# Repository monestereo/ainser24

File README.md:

##Eagle-Files for a 24 input multiplexer using the Microchip MCP3208 i2c ADC

For more information and licensing visit: [ucapps/midibox](http://www.ucapps.de/mbhp_ainser64.html)

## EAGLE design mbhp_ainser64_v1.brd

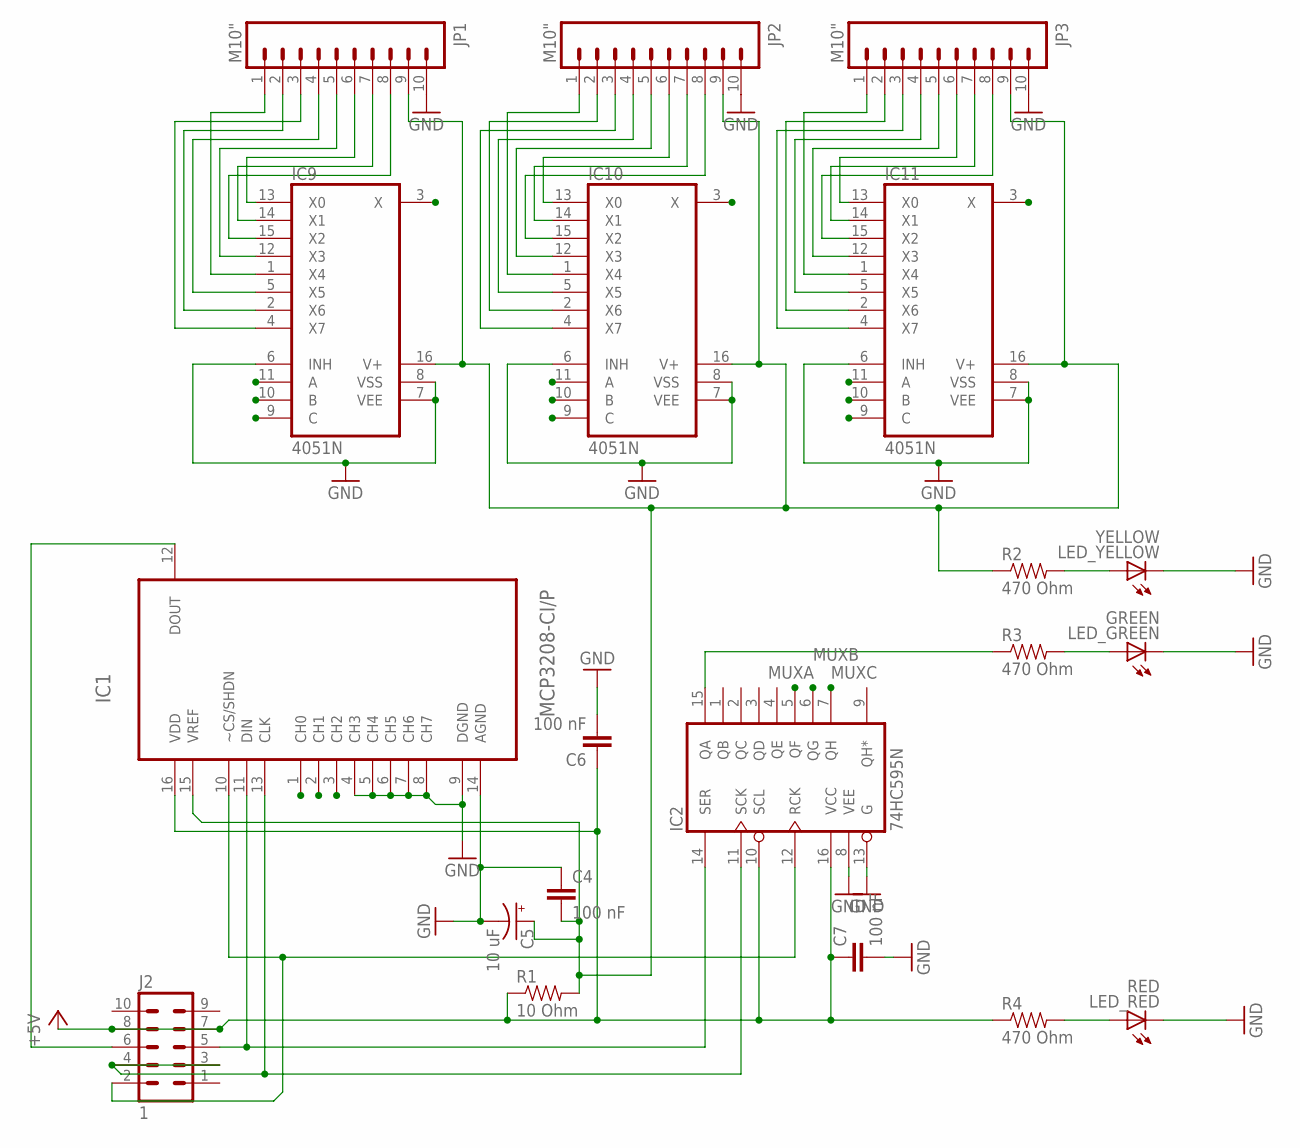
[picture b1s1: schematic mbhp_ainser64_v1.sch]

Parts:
C4, C6, C7: 100 nF; CAP-PTH-5MM
C5: 10 uF; CPOL-RADIAL-10UF-25V
IC1: MCP3208-CI/P; DIP254P762X432-16
IC2: 74HC595N; DIL16
IC9, IC10, IC11: 4051N; DIL16
J2: 1; MA05-2
JP1, JP2, JP3: M10"; 1X10
LED_GREEN: GREEN; LED3MM-NS
LED_RED: RED; LED3MM-NS
LED_YELLOW: YELLOW; LED3MM-NS
R1: 10 Ohm; AXIAL-0.3
R2, R3, R4: 470 Ohm; AXIAL-0.3

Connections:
+5V: C6.1, C7.1, IC1.16 (VDD), IC2.10 (SCL), IC2.16 (VCC), J2.7, J2.8, R1.P$1 (1), R4.P$1 (1)
CH0: IC1.1 (CH0), IC11.3 (X)
CH1: IC1.2 (CH1), IC10.3 (X)
CH2: IC1.3 (CH2), IC9.3 (X)
GND: C4.1, C5.2 (-), C6.2, C7.2, IC1.4 (CH3), IC1.5 (CH4), IC1.6 (CH5), IC1.7 (CH6), IC1.8 (CH7), IC1.9 (DGND), IC1.14 (AGND), IC2.8 (VEE), IC2.13 (G), IC9.6 (INH), IC9.7 (VEE), IC9.8 (VSS), IC10.6 (INH), IC10.7 (VEE), IC10.8 (VSS), IC11.6 (INH), IC11.7 (VEE), IC11.8 (VSS), JP1.10, JP2.10, JP3.10, LED_GREEN.K (C), LED_RED.K (C), LED_YELLOW.K (C)
MUXA: IC2.5 (QF), IC9.9 (C), IC10.9 (C), IC11.9 (C)
MUXB: IC2.6 (QG), IC9.10 (B), IC10.10 (B), IC11.10 (B)
MUXC: IC2.7 (QH), IC9.11 (A), IC10.11 (A), IC11.11 (A)
unnamed: IC1.10 (~CS/SHDN), IC2.12 (RCK), J2.2
unnamed: IC1.13 (CLK), IC2.11 (SCK), J2.3, J2.4
unnamed: IC1.11 (DIN), IC2.14 (SER), J2.5
unnamed: LED_RED.A, R4.P$2 (2)
unnamed: IC1.12 (DOUT), J2.6
unnamed: C4.2, C5.1 (+), IC1.15 (VREF), IC9.16 (V+), IC10.16 (V+), IC11.16 (V+), JP1.9, JP2.9, JP3.9, R1.P$2 (2), R2.P$1 (1)
unnamed: LED_GREEN.A, R3.P$2 (2)
unnamed: IC2.15 (QA), R3.P$1 (1)
unnamed: IC10.13 (X0), JP2.6
unnamed: IC10.14 (X1), JP2.7
unnamed: IC10.15 (X2), JP2.8
unnamed: IC10.12 (X3), JP2.5
unnamed: IC10.5 (X5), JP2.4
unnamed: IC10.4 (X7), JP2.3
unnamed: IC10.2 (X6), JP2.2
unnamed: IC10.1 (X4), JP2.1
unnamed: IC11.15 (X2), JP3.8
unnamed: IC11.14 (X1), JP3.7
unnamed: IC11.13 (X0), JP3.6
unnamed: IC11.12 (X3), JP3.5
unnamed: IC11.5 (X5), JP3.4
unnamed: IC11.4 (X7), JP3.3
unnamed: IC11.2 (X6), JP3.2
unnamed: IC11.1 (X4), JP3.1
unnamed: IC9.15 (X2), JP1.8
unnamed: IC9.14 (X1), JP1.7
unnamed: IC9.13 (X0), JP1.6
unnamed: IC9.12 (X3), JP1.5
unnamed: IC9.5 (X5), JP1.4
unnamed: IC9.4 (X7), JP1.3
unnamed: IC9.2 (X6), JP1.2
unnamed: IC9.1 (X4), JP1.1
unnamed: LED_YELLOW.A, R2.P$2 (2)

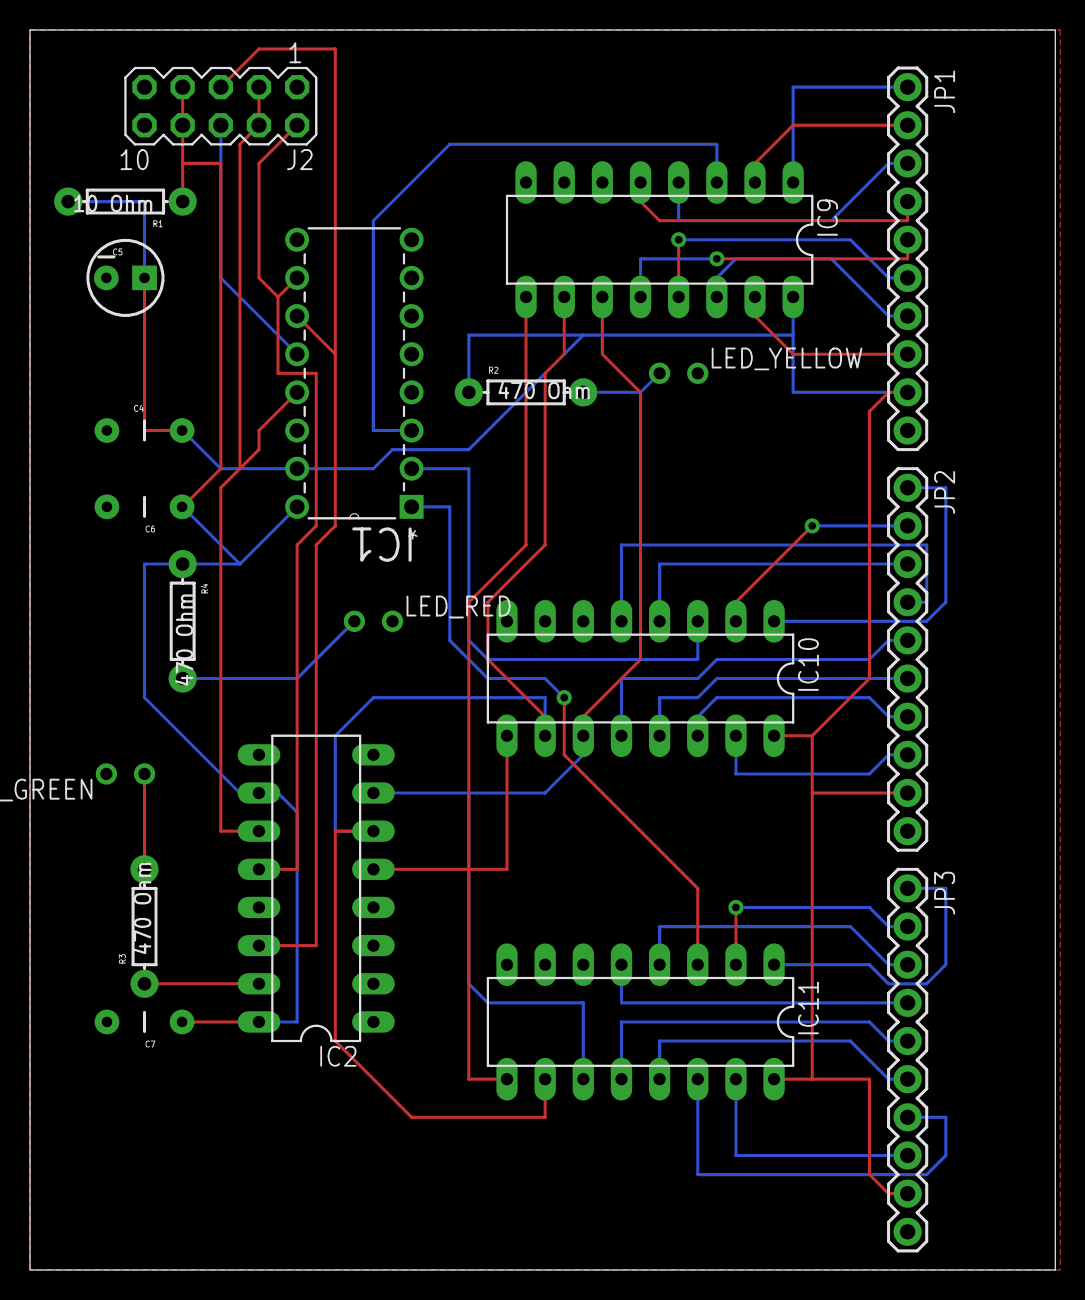
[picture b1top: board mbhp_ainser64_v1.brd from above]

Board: 2 copper layers, 68.2 x 82.5 mm, 24 parts (0 on the bottom side), 41 nets.

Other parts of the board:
U$1, U$2: ANGLE-ARROW-NW1
U$3, U$4: ANGLE-ARROW-NW1-16

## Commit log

2014-03-13 design ready

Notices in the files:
parts and their libraries:
SparkFun-Capacitors: Licensing: Creative Commons ShareAlike 4.0 International - https://creativecommons.org/licenses/by-sa/4.0
